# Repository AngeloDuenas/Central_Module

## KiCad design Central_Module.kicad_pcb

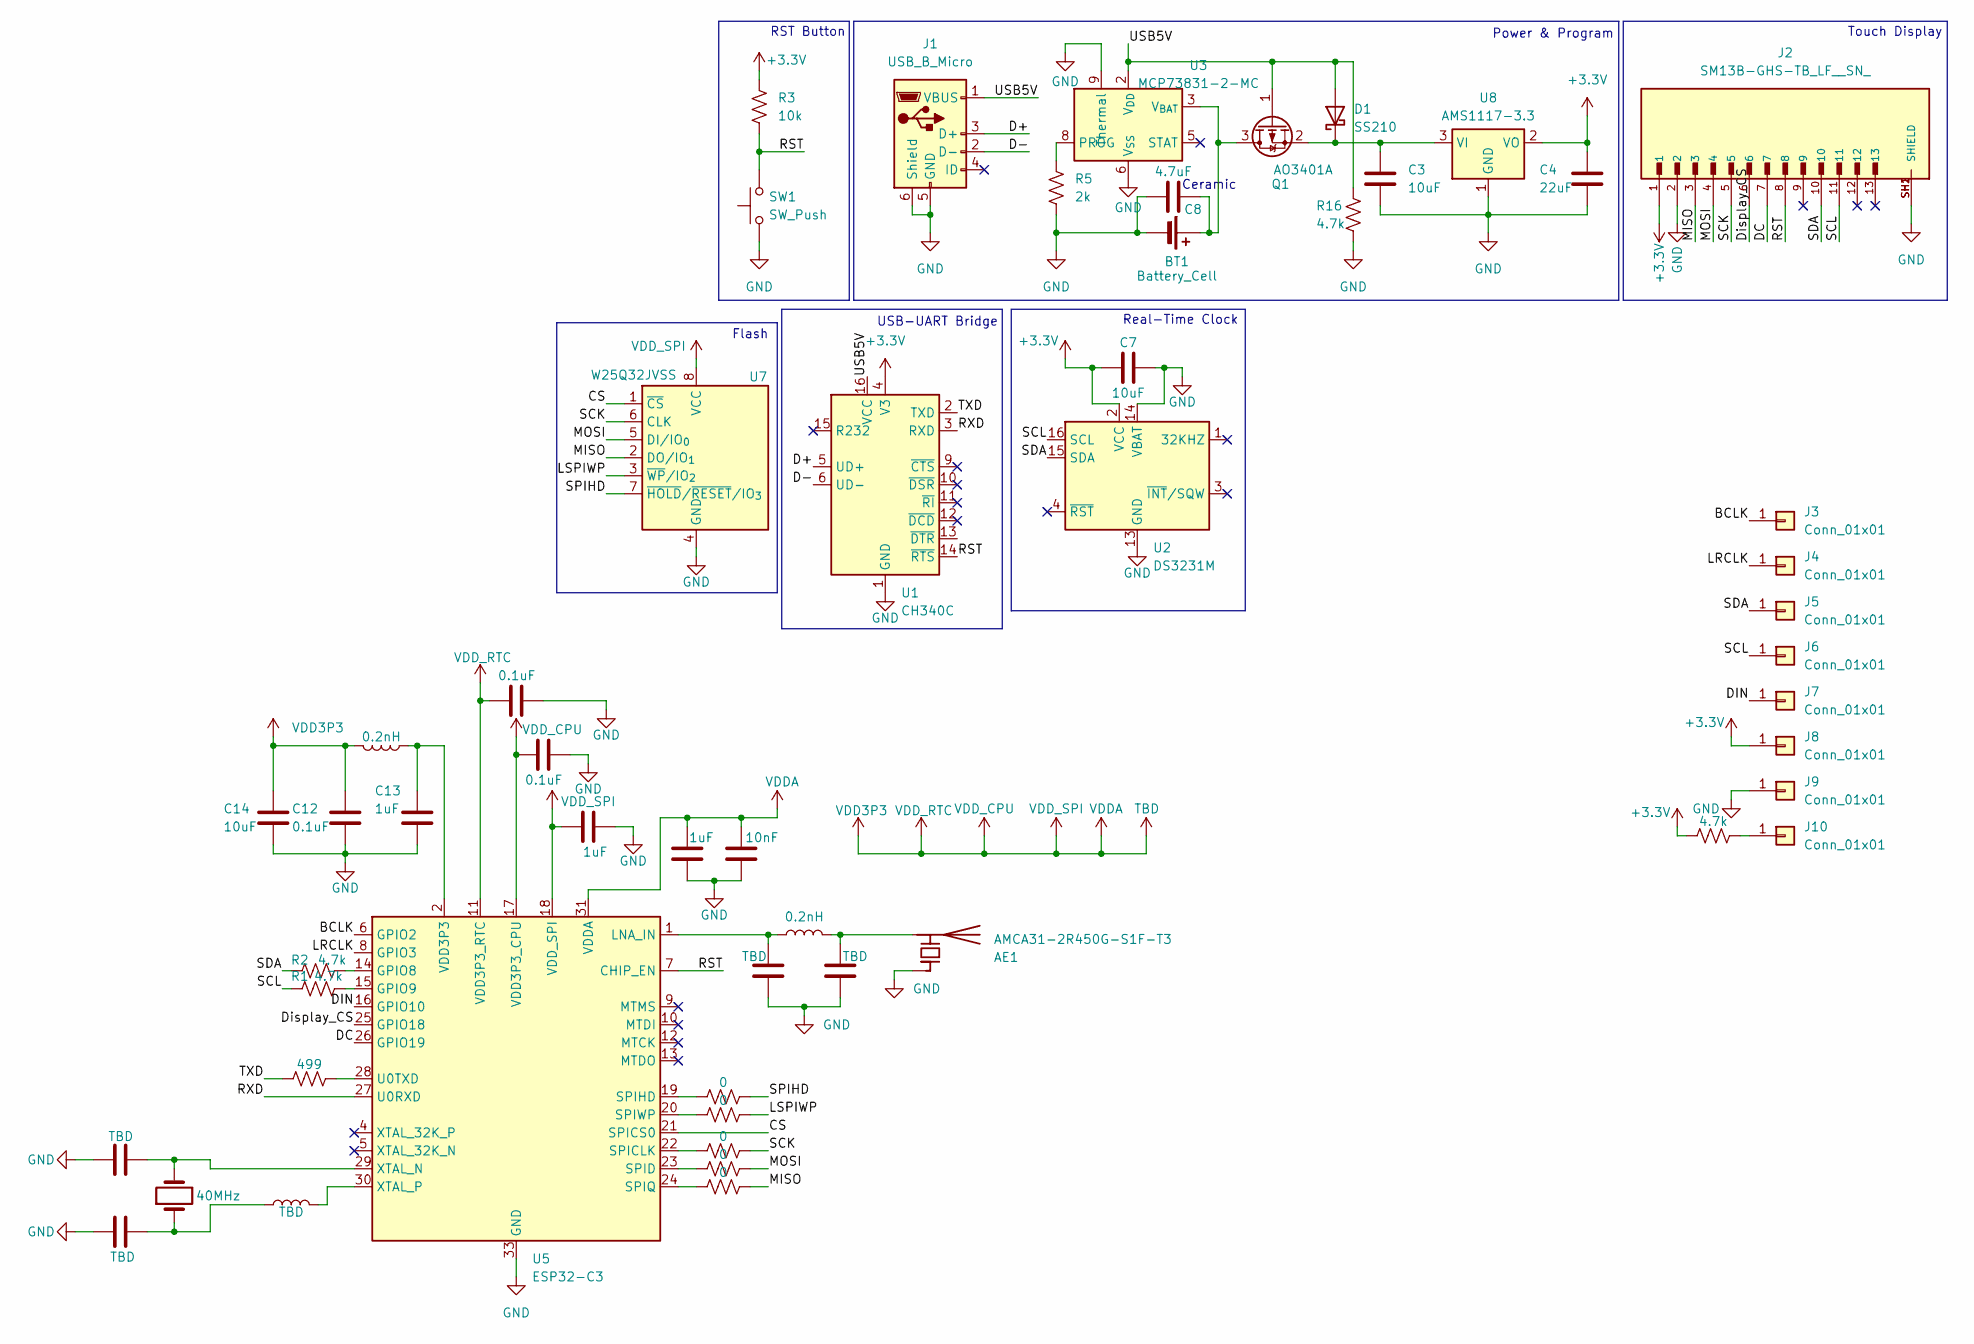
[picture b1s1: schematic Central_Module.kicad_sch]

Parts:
AE1: AMCA31-2R450G-S1F-T3; XDCR_AMCA31-2R450G-S1F-T3
BT1: Battery_Cell; PinHeader_1x02_P1.00mm_Vertical
C3, C7, C14: 10uF; C_0402_1005Metric
C4: 22uF; C_0402_1005Metric
C8: 4.7uF; C_0402_1005Metric
C10, C11, C20, C21: TBD; C_0402_1005Metric
C12, C15, C16: 0.1uF; C_0402_1005Metric
C13, C17, C18: 1uF; C_0402_1005Metric
C19: 10nF; C_0402_1005Metric
D1: SS210; D_SMA
J1: USB_B_Micro; USB_Micro-B_Molex-105017-0001
J2: SM13B-GHS-TB_LF__SN_; JST_SM13B-GHS-TB_LF__SN_; PARTREV 18/3/21
J3, J4, J5, J6, J7, J8, J9, J10: Conn_01x01; 1mm Pad
L1, L2: 0.2nH; L_0402_1005Metric
L3: TBD; L_0402_1005Metric
Q1: AO3401A; SOT-23
R1, R2, R4, R16: 4.7k; R_0402_1005Metric
R3: 10k; R_0402_1005Metric
R5: 2k; R_0402_1005Metric
R9, R10, R11, R12, R13: 0; R_0402_1005Metric
R14: 499; R_0402_1005Metric
SW1: SW_Push; SW_SPST_TL3342
U1: CH340C; SOIC-16_3.9x9.9mm_P1.27mm
U2: DS3231M; SOIC-16W_7.5x10.3mm_P1.27mm
U3: MCP73831-2-MC; DFN-8-1EP_3x2mm_P0.5mm_EP1.7x1.4mm
U5: ESP32-C3; QFN-32-1EP_5x5mm_P0.5mm_EP3.7x3.7mm
U7: W25Q32JVSS; SOIC-8_5.3x5.3mm_P1.27mm
U8: AMS1117-3.3; SOT-223-3_TabPin2
Y1: 40MHz; Crystal_SMD_3215-2Pin_3.2x1.5mm

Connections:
+3.3V: C4.2, C7.2, J2.1, J8.1, R3.1, R4.1, U1.4 (V3), U2.2 (VCC), U8.2 (VO)
/BCLK: J3.1, U5.6 (GPIO2)
/CS: U5.21 (SPICS0), U7.1 (~CS)
/D+: J1.3 (D+), U1.5 (UD+)
/D-: J1.2 (D-), U1.6 (UD-)
/DC: J2.7, U5.26 (GPIO19)
/DIN: J7.1, U5.16 (GPIO10)
/Display_CS: J2.6, U5.25 (GPIO18)
/LRCLK: J4.1, U5.8 (GPIO3)
/LSPIWP: R10.2, U7.3 (~WP/IO_{2})
/MISO: J2.3, R13.2, U7.2 (DO/IO_{1})
/MOSI: J2.4, R12.2, U7.5 (DI/IO_{0})
/RST: J2.8, R3.2, SW1.2, U1.14 (~RTS), U5.7 (CHIP_EN)
/RXD: U1.3 (RXD), U5.27 (U0RXD)
/SCK: J2.5, R11.2, U7.6 (CLK)
/SCL: J2.11, J6.1, R1.1, U2.16 (SCL)
/SDA: J2.10, J5.1, R2.1, U2.15 (SDA)
/SPIHD: R9.2, U7.7 (~HOLD/~RESET/IO_{3})
/TXD: R14.1, U1.2 (TXD)
/USB5V: D1.2 (A), J1.1 (VBUS), Q1.1 (G), R16.1, U1.16 (VCC), U3.1 (V_{DD}), U3.2 (V_{DD})
GND: AE1.1 (FEED), BT1.2 (-), C3.2, C4.1, C7.1, C8.2, C10.2, C11.2, C12.2, C13.2, C14.2, C15.2, C16.2, C17.2, C18.1, C19.1, C20.2, C21.2, J1.5 (GND), J1.6 (Shield), J2.2, J2.SH1 (SHIELD), J2.SH2 (SHIELD), J9.1, R5.2, R16.2, SW1.1, U1.1 (GND), U2.5 (GND), U2.6 (GND), U2.7 (GND), U2.8 (GND), U2.9 (GND), U2.10 (GND), U2.11 (GND), U2.12 (GND), U2.13 (GND), U2.14 (VBAT), U3.6 (V_{SS}), U3.9 (Thermal), U5.33 (GND), U7.4 (GND), U8.1 (GND)
unnamed: AE1.2 (PCB_Trace), C11.1, L1.2
unnamed: BT1.1 (+), C8.1, Q1.3 (D), U3.3 (V_{BAT}), U3.4 (V_{BAT})
unnamed: C13.1, L2.1, U5.2 (VDD3P3), U5.3 (VDD3P3)
unnamed: C21.1, L3.1, Y1.1
unnamed: C3.1, D1.1 (K), Q1.2 (S), U8.3 (VI)
unnamed: J10.1, R4.2
unnamed: R5.1, U3.8 (PROG)
unnamed: R2.2, U5.14 (GPIO8)
unnamed: R1.2, U5.15 (GPIO9)
unnamed: C10.1, L1.1, U5.1 (LNA_IN)
unnamed: R11.1, U5.22 (SPICLK)
unnamed: R12.1, U5.23 (SPID)
unnamed: R9.1, U5.19 (SPIHD)
unnamed: R13.1, U5.24 (SPIQ)
unnamed: R10.1, U5.20 (SPIWP)
unnamed: R14.2, U5.28 (U0TXD)
unnamed: C20.1, U5.29 (XTAL_N), Y1.2
unnamed: L3.2, U5.30 (XTAL_P)
TBD: C12.1, C14.1, C15.1, C16.1, C17.1, C18.2, C19.2, L2.2, U5.11 (VDD3P3_RTC), U5.17 (VDD3P3_CPU), U5.18 (VDD_SPI), U5.31 (VDDA), U5.32 (VDDA), U7.8 (VCC)

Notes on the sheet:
Flash
USB-UART Bridge
Touch Display
Power & Program
Real-Time Clock
Ceramic
RST Button

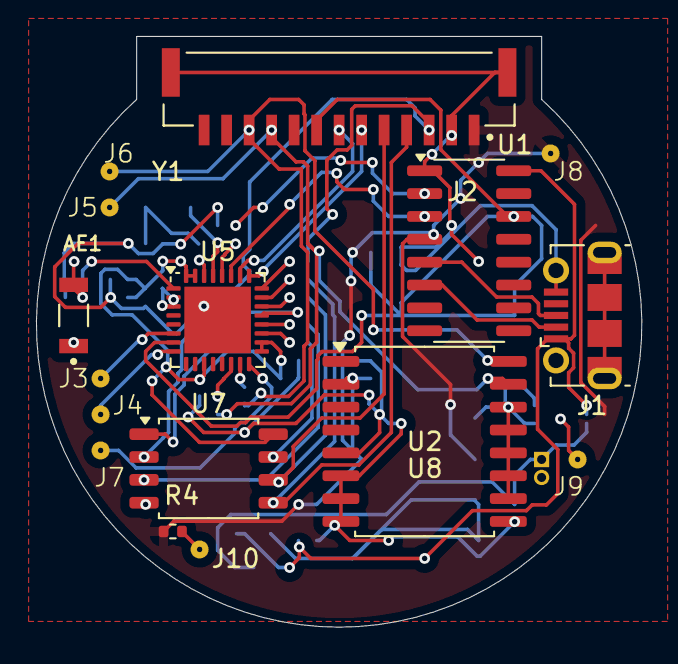
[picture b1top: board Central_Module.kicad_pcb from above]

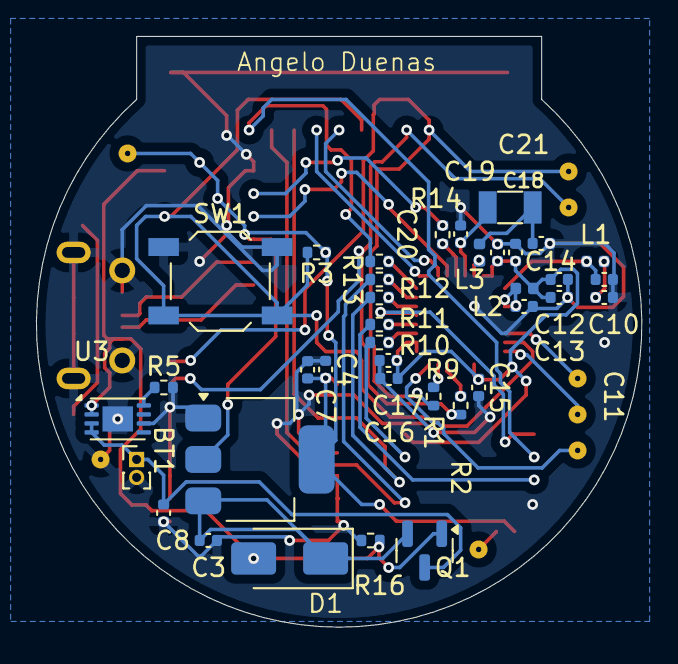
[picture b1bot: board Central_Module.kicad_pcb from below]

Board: 2 copper layers, 33.6 x 32.8 mm, 53 parts (37 on the bottom side), 40 nets.

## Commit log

2025-09-29 Pre-Violations DRC Corrections
2025-09-29 Post DRC Checker
2025-10-15 ForReview
